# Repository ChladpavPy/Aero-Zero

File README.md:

# Aero-Zero Custom Flight Controller

I started this project, because I wanted to build fully autonomous ai drone. When I looked at the flight controllers available on the market, they were full of hardware that I just do not need or just that I could not add things that I want (for example the Rasberry pi zero 2w) . Most boards also waste a lot of space on powering analog OSD chips, which is completely useless for me because I am flying a purely digital HD system like Walksnail Avatar. Because the technology changed and digital is the standard now, I realized it is just a waste of space to keep the analog stuff and massive connectors.

I am using Raspberry Pi Zero 2W as the computer. Firstly I wanted to use something more powerful to be able to run ai smoother, like allwinner cubie a7z, but it is more expensive and the biggest issue is the firmware and gpio programming on this device. I have no idea, how I would programm this device, when there are basically no manuals or datasheets to this, so I am using the basic raspberry pi zero 2w. So the most interesting thing on this pcb is the pi zero 2w, which is connected to the board by set of pins and screw holes that can be mounted on the pcb by screws.

The drone itself would be able to lift off and fly to a location based on the gps, there is the barometer, from which the drone gets the current altitude and can get to ground. I am using walksnail camera and elrs, plus LIDAR. There is a jst connector for led strip, while at the same time there are built in leds on the drone chassis, esc unit connector and built in electromagnetic buzzer and boot and rst buttons.

The first stage was actually studying the STM32 pinouts and figuring out as much possible of how modern flight controllers handle gyro SPI communication and high speed SDIO routing.

A custom mainboard designed to replace standard generic flight controllers. Built to handle Betaflight high speed kinematics and communicate directly with a Raspberry Pi Zero 2W. Designed entirely from scratch in KiCad 10.

## Project Features

* **Microcontroller:** STM32F405 (100-pin, 32-bit ARM Cortex-M4)
* **Stackup:** 4-Layer PCB (Signal / GND / GND+Power / Signal) for internal routing and better EMI shielding against switching inductors
* **IMU (Gyro):** TDK InvenSense ICM-42688-P connected via dedicated hardware SPI1 bus for high-speed kinematics
* **Barometer:** Goertek SPL06-007 on-board sensor for accurate altitude telemetry
* **Power:** VBAT main input with robust 5V switching regulator (TPS54302) and isolated 3.3V sensor rails
* **Connectivity:** USB-C for main communication with USBLC6 ESD protection, native Raspberry Pi UART interface
* **Digital Video:** Dedicated Walksnail/Caddx VTX JST-SH port (Analog OSD intentionally removed to save space)
* **Storage:** Integrated MicroSD slot (Hirose Push-Pull) routed via high-speed 4-bit SDIO bus for blackbox logging
* **Hardware Protections:** Strict 1:1 hardware pin layout for GPS and LiDAR connectors to prevent accidental voltage shorts during assembly
* **Radio Link:** Dedicated UART port for 2.4GHz ExpressLRS nano receiver.

## Firmware

Since this board is built around a custom STM32F405 microcontroller, it runs on the open-source [Betaflight](https://github.com/betaflight/betaflight) firmware. Instead of writing custom flight control loops from scratch, the firmware setup uses a custom target configuration. You can find the complete pin-mapping and resource file (`AeroZero_BF_Config.txt`) ready in the `Firmware` folder.

## Gallery

### 3D PCB Render

### PCB 

### Schematics

### Mechanical Integration MARK4

### Mechanical Integration CUSTOM AERO-ZERO CAD

---

## Bill of Materials (BOM)

| Component | Qty | Purpose / Description | Price (USD) | Link / Distributor |
| :--- | :---: | :--- | :--- | :--- |
| **Custom PCBA (Aero-Zero)** | 2 | Custom designed 4-layer STM32 flight controller board. Fully assembled via JLCPCB SMT. | $131.50 | JLCPCB |
| **GEPRC GEP-M1025-DQ GPS** | 1 | High-precision positioning data (u-blox M10) with integrated QMC5883L compass and backup DPS310 barometer. | $19.80 | [Banggood](https://www.banggood.com/cs/GEPRC-GEP-M1025-Series-M10-Chip-GPS-Module-for-RC-Drone-FPV-Racing-Helicopter-Quadcopter-RC-Airplane-Car-p-2000868.html?cur_warehouse=CN&ID=6324596&rmmds=search) |
| **SpeedyBee BLS 60A 30x30 4-in-1 ESC** | 1 | Electronic Speed Controller (4-in-1) for driving the primary flight motors | $44.00 | [AliExpress](https://www.aliexpress.com/item/1005010400734832.html) |
| **EMAX ECO II 2207 1700KV Brushless Motor** | 4 | Primary propulsion system providing lift and flight dynamics for the drone chassis | $59.00 | [AliExpress](https://www.aliexpress.com/item/1005001706267138.html) |
| **Raspberry Pi Zero 2 W** | 1 | Secondary AI and computer vision processing unit for autonomous flight capabilities | $20.17 | [RPiShop (Czech Republic)](https://rpishop.cz/raspberry-pi-zero/4311-raspberry-pi-zero-2-w.html) |
| **BETAFPV Nano 2.4GHz ELRS** | 1 | 2.4GHz ExpressLRS receiver with T-Type antenna for reliable, low-latency radio control link. | $9.07 | [Aliexpress](https://a.aliexpress.com/_EHLASWw) |
| **LCSC Discrete Components** | 1 | Bottom-side passive components (SD slot, buzzer, flyback diode, resistors/capacitors) for manual assembly. | $16.21 | lcsc.com |

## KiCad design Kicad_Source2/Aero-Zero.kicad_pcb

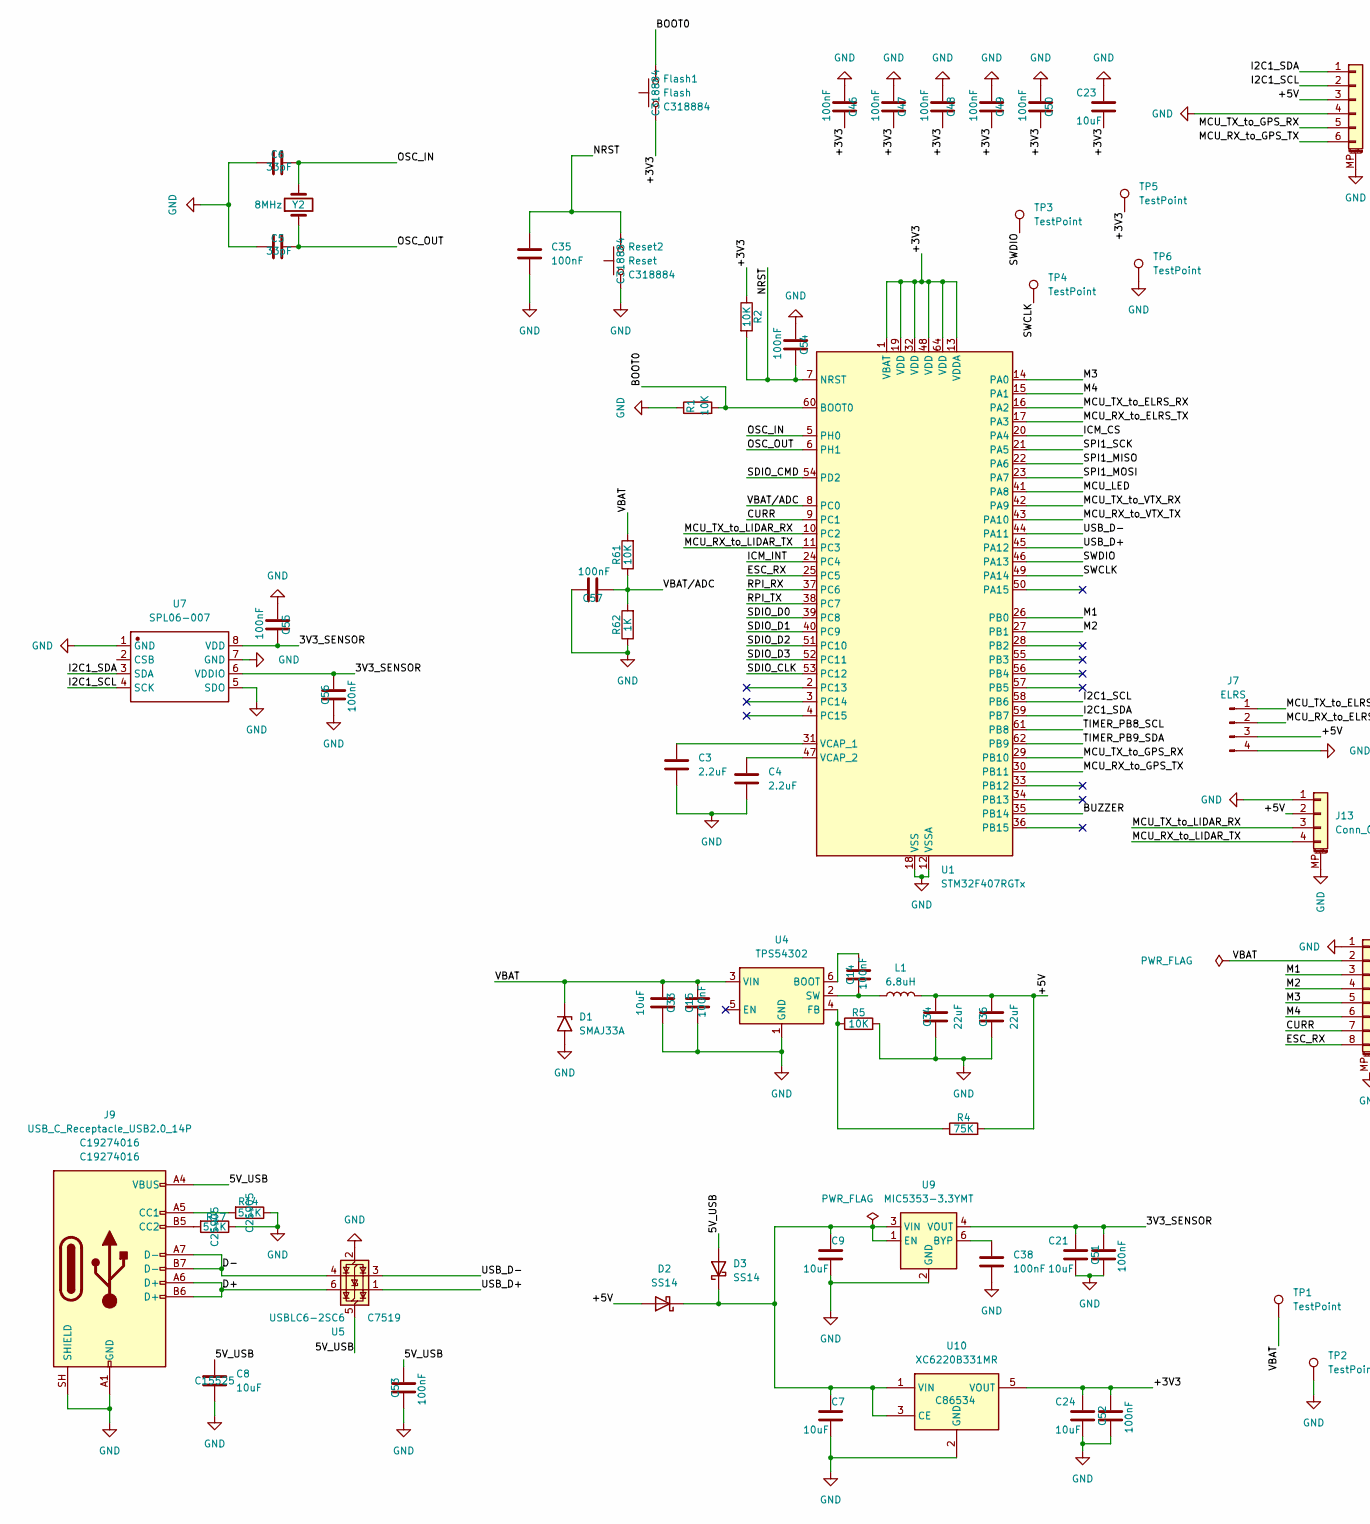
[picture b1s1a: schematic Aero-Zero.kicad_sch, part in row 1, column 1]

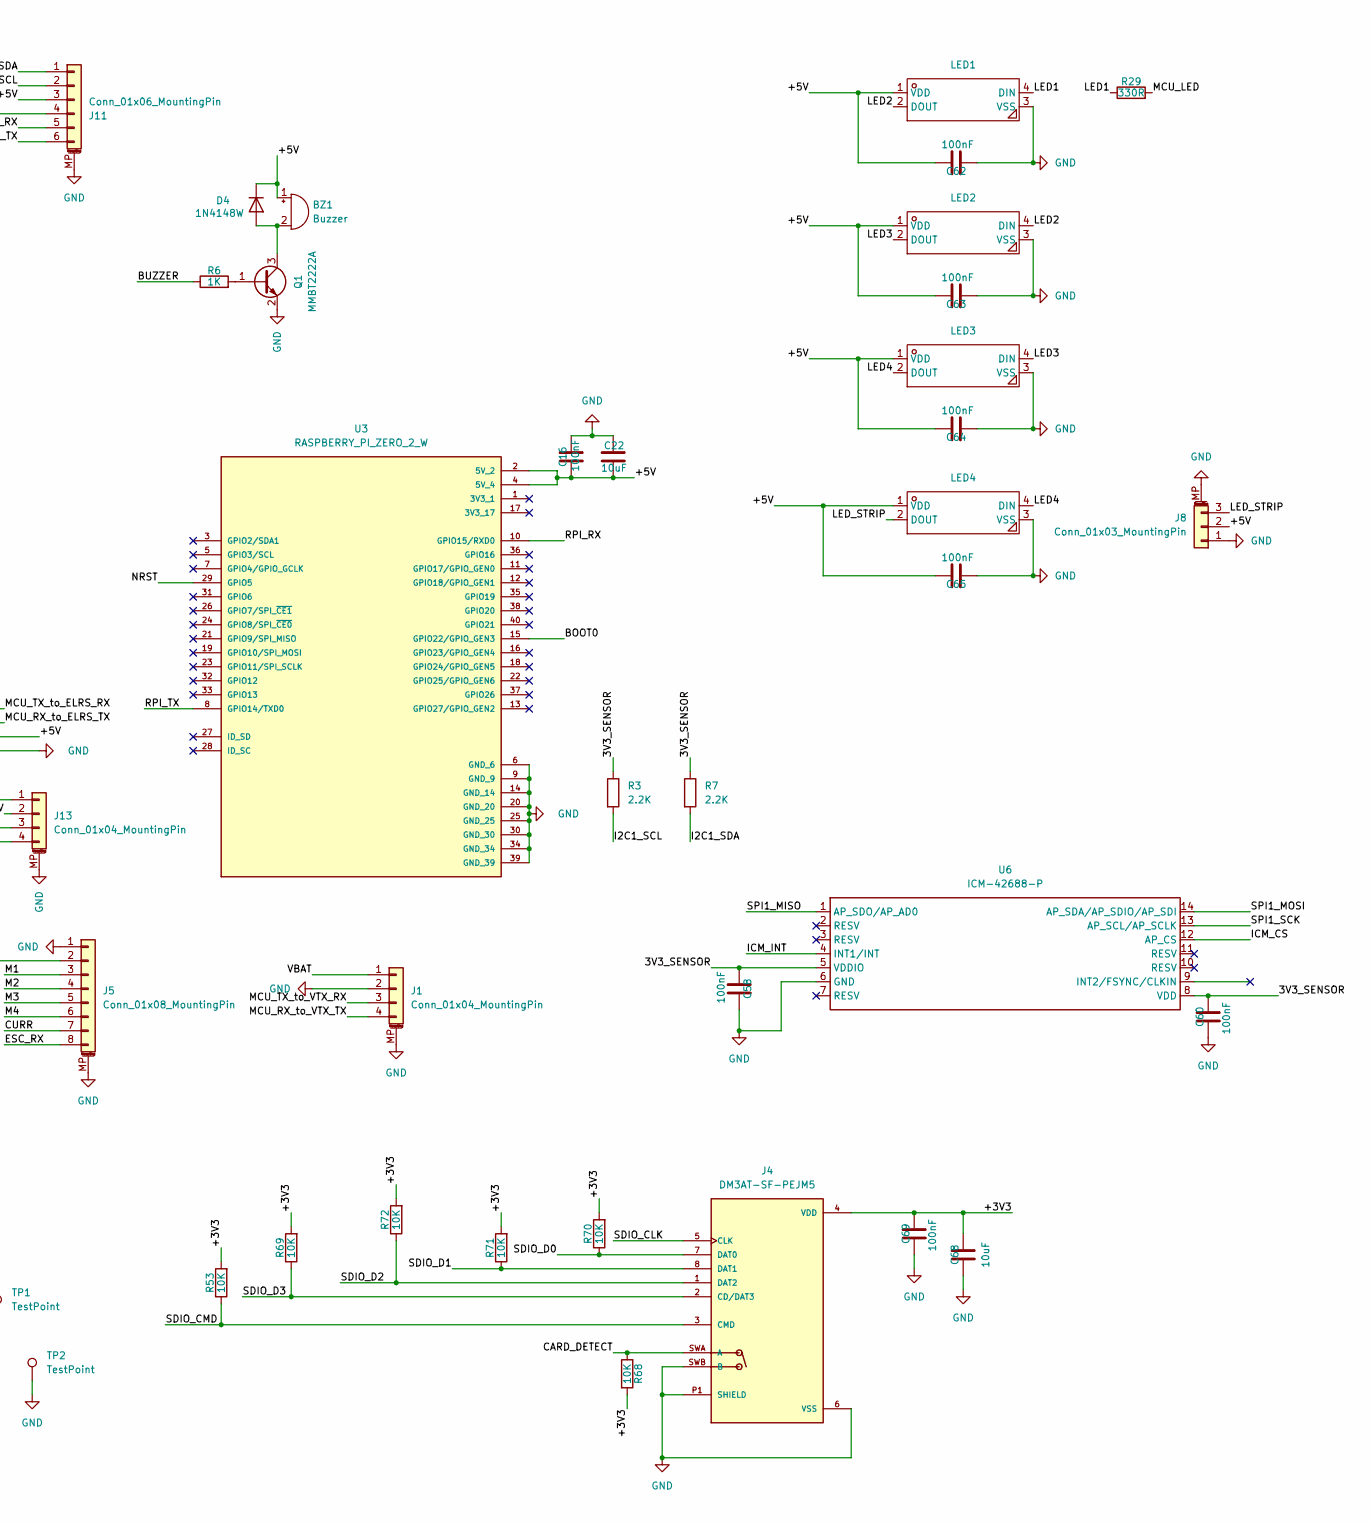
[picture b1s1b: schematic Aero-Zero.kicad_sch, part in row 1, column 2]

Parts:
BZ1: Buzzer; BUZ-SMD_4P-L8.5-W8.5-TL; LCSC C556939
C3, C4: 2.2uF; C_0603_1608Metric; LCSC C23630
C5, C6: 33pF; C_0402_1005Metric; LCSC C1562
C7, C33, C68: 10uF; C_0603_1608Metric; LCSC C19702
C8: 10uF; C_0402_1005Metric; LCSC C15525
C9: 10uF; C_0603_1608Metric; MNF PART NUMBER C15525; LCSC C19702
C14, C15, C16, C46, C47, C48, C49, C50, C51, C52, C53, C54, C55, C56, C57, C58, C60, C62, C63, C64, C65: 100nF; C_0402_1005Metric; LCSC C307331
C21, C24: 10uF; C_0402_1005Metric; MNF PART NUMBER C15525; LCSC C15525
C22, C23: 10uF; C_0805_2012Metric; MNF PART NUMBER C15850; LCSC C15850
C34, C36: 22uF; C_0805_2012Metric; LCSC C45783
C35: 100nF; C_0603_1608Metric; MNF PART NUMBER C14663; LCSC C14663
C38: 100nF; C_0402_1005Metric; MNF PART NUMBER C307331; LCSC C307331
C69: 100nF; C_0603_1608Metric; LCSC C14663
D1: SMAJ33A; D_SMA; LCSC C113966
D2, D3: SS14; D_SMA; LCSC C2480
D4: 1N4148W; D_SOD-123; LCSC C81598
Flash1: Flash; SW_Push_1P1T_XKB_TS-1187A; MNF PART NUMBER C318884; LCSC C318884
J1: Conn_01x04_MountingPin; JST_SH_SM04B-SRSS-TB_1x04-1MP_P1.00mm_Horizontal
J4: DM3AT-SF-PEJM5; HRS_DM3AT-SF-PEJM5_card; PARTREV 20200913; DigiKey_Part_Number HR1964CT-ND
J5: Conn_01x08_MountingPin; JST_SH_SM08B-SRSS-TB_1x08-1MP_P1.00mm_Horizontal
J7: ELRS; PinSocket_1x04_P2.54mm_Vertical
J8: Conn_01x03_MountingPin; JST_SH_SM03B-SRSS-TB_1x03-1MP_P1.00mm_Horizontal
J9: USB_C_Receptacle_USB2.0_14P; USB_C_Receptacle_HCTL_HC-TYPE-C-16P-01A; MNF PART NUMBER C19274016; LCSC C19274016
J11: Conn_01x06_MountingPin; JST_SH_SM06B-SRSS-TB_1x06-1MP_P1.00mm_Horizontal
J13: Conn_01x04_MountingPin; JST_GH_SM04B-GHS-TB_1x04-1MP_P1.25mm_Horizontal
L1: 6.8uH; IND-SMD_L6.0-W6.0_SWPA6045S; LCSC C57254
LED1, LED2, LED3, LED4: LED-SMD_4P-L3.5-W3.5-TL_WS2812B; Manufacturer Part WS2812B-B/T; LCSC Part Name RGB三色
Q1: MMBT2222A; SOT-23; LCSC C8512
R1, R5, R61: 10K; R_0402_1005Metric; LCSC C25804
R2: 10K; C_0603_1608Metric; LCSC C25804
R3, R7: 2.2K; R_0402_1005Metric; LCSC C25879
R4: 75K; R_0603_1608Metric; LCSC C23242
R6: 1K; R_0603_1608Metric; LCSC C21190
R14, R17: 5.1K; R_0402_1005Metric; MNF PART NUMBER C25905; LCSC C25905
R29: 330R; R_0402_1005Metric; LCSC C25104
R53, R68, R69, R70, R71, R72: 10K; R_0603_1608Metric; LCSC C25804
R62: 1K; R_0402_1005Metric; LCSC C11702
Reset2: Reset; SW_Push_1P1T_XKB_TS-1187A; MNF PART NUMBER C318884; LCSC C318884
TP1, TP2: TestPoint; TestPoint_THTPad_D3.0mm_Drill1.5mm
TP3, TP4, TP5, TP6: TestPoint; TestPoint_Pad_1.0x1.0mm
U1: STM32F407RGTx; LQFP-64_10x10mm_P0.5mm; LCSC C15742
U3: RASPBERRY_PI_ZERO_2_W; RpiZero2W_Redukce_Final; PARTREV April 2024
U4: TPS54302; SOT-23-6; LCSC C311983
U5: USBLC6-2SC6; SOT-23-6; MNF PART NUMBER C7519; LCSC C7519
U6: ICM-42688-P; LGA-14_L3.0-W2.5-P0.50-TL; Manufacturer Part ICM-42688-P; LCSC C1850418
U7: SPL06-007; SENSOR-SMD_SPL06-007; Manufacturer Part SPL06-007; LCSC C233787
U9: MIC5353-3.3YMT; MLF-6-1EP_1.6x1.6mm_P0.5mm_EP0.5x1.26mm; LCSC C511311
U10: XC6220B331MR; SOT-23-5; MNF PART NUMBER C86534; LCSC C86534
Y2: 8MHz; Crystal_SMD_5032-2Pin_5.0x3.2mm; LCSC C115962

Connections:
/3V3_SENSOR: C21.1, C51.1, C55.1, C56.1, C58.2, C60.1, R3.1, R7.1, U6.5 (VDDIO), U6.8 (VDD), U7.6 (VDDIO), U7.8 (VDD), U9.4 (VOUT); also elsewhere on the board
/5V_USB: C8.1, C53.1, D3.2 (A), J9.A4 (VBUS), J9.A9 (VBUS), J9.B4 (VBUS), J9.B9 (VBUS), U5.5 (VBUS)
/+3V3: C23.2, C24.1, C46.1, C47.1, C48.1, C49.1, C50.1, C52.1, C68.1, C69.1, Flash1.1, J4.4 (VDD), R2.1, R53.2, R68.2, R69.2, R70.2, R71.2, R72.2, TP5.1 (1_1), U1.1 (VBAT), U1.13 (VDDA), U1.19 (VDD), U1.32 (VDD), U1.48 (VDD), U1.64 (VDD), U10.5 (VOUT); also elsewhere on the board
/+5V: BZ1.1 (+), C16.2, C22.2, C34.1, C36.1, C62.1, C63.1, C64.1, C65.1, D2.2 (A), D4.1 (K), J7.3, J8.2, J11.3, J13.2, L1.2, LED1.1 (VDD), LED2.1 (VDD), LED3.1 (VDD), LED4.1 (VDD), R4.2, U3.2 (5V_2), U3.4 (5V_4)
/BOOT0: Flash1.2, R1.2, U1.60 (BOOT0), U3.15 (GPIO22/GPIO_GEN3)
/BUZZER: R6.1, U1.35 (PB14)
/CARD_DETECT: J4.SWA (A), R68.1
/CURR: J5.7, U1.9 (PC1)
/D+: J9.A6 (D+), J9.B6 (D+), U5.6 (I/O1)
/D-: J9.A7 (D-), J9.B7 (D-), U5.4 (I/O2)
/ESC_RX: J5.8, U1.25 (PC5)
/I2C1_SCL: J11.2, R3.2, U1.58 (PB6), U7.4 (SCK); also elsewhere on the board
/I2C1_SDA: J11.1, R7.2, U1.59 (PB7), U7.3 (SDA); also elsewhere on the board
/ICM_CS: U1.20 (PA4), U6.12 (AP_CS)
/ICM_INT: U1.24 (PC4), U6.4 (INT1/INT)
/LED1: LED1.4 (DIN), R29.1
/LED2: LED1.2 (DOUT), LED2.4 (DIN)
/LED3: LED2.2 (DOUT), LED3.4 (DIN)
/LED4: LED3.2 (DOUT), LED4.4 (DIN)
/LED_STRIP: J8.3, LED4.2 (DOUT)
/M1: J5.3, U1.26 (PB0)
/M2: J5.4, U1.27 (PB1)
/M3: J5.5, U1.14 (PA0)
/M4: J5.6, U1.15 (PA1)
/MCU_LED: R29.2, U1.41 (PA8)
/MCU_RX_to_ELRS_TX: J7.2, U1.17 (PA3)
/MCU_RX_to_GPS_TX: J11.6, U1.30 (PB11)
/MCU_RX_to_LIDAR_TX: J13.4, U1.11 (PC3)
/MCU_RX_to_VTX_TX: J1.4, U1.43 (PA10)
/MCU_TX_to_ELRS_RX: J7.1, U1.16 (PA2)
/MCU_TX_to_GPS_RX: J11.5, U1.29 (PB10)
/MCU_TX_to_LIDAR_RX: J13.3, U1.10 (PC2)
/MCU_TX_to_VTX_RX: J1.3, U1.42 (PA9)
/NRST: C35.1, C54.1, R2.2, Reset2.2, U1.7 (NRST), U3.29 (GPIO5)
/OSC_IN: C6.1, U1.5 (PH0), Y2.2
/OSC_OUT: C5.1, U1.6 (PH1), Y2.1
/RPI_RX: U1.37 (PC6), U3.10 (GPIO15/RXD0)
/RPI_TX: U1.38 (PC7), U3.8 (GPIO14/TXD0)
/SDIO_CLK: J4.5 (CLK), U1.53 (PC12)
/SDIO_CMD: J4.3 (CMD), R53.1, U1.54 (PD2)
/SDIO_D0: J4.7 (DAT0), R70.1, U1.39 (PC8)
/SDIO_D1: J4.8 (DAT1), R71.1, U1.40 (PC9)
/SDIO_D2: J4.1 (DAT2), R72.1, U1.51 (PC10)
/SDIO_D3: J4.2 (CD/DAT3), R69.1, U1.52 (PC11)
/SPI1_MISO: U1.22 (PA6), U6.1 (AP_SDO/AP_AD0)
/SPI1_MOSI: U1.23 (PA7), U6.14 (AP_SDA/AP_SDIO/AP_SDI)
/SPI1_SCK: U1.21 (PA5), U6.13 (AP_SCL/AP_SCLK)
/SWCLK: TP4.1 (1_1), U1.49 (PA14)
/SWDIO: TP3.1 (1_1), U1.46 (PA13)
/TIMER_PB8_SCL: U1.61 (PB8)
/TIMER_PB9_SDA: U1.62 (PB9)
/USB_D+: U1.45 (PA12), U5.1 (I/O1)
/USB_D-: U1.44 (PA11), U5.3 (I/O2)
/VBAT: C15.1, C33.2, D1.1 (A1), J1.1, J5.2, R61.2, TP1.1 (1_1), U4.3 (VIN)
/VBAT/ADC: C57.2, R61.1, R62.2, U1.8 (PC0)
GND: C3.1, C4.2, C5.2, C6.2, C7.2, C8.2, C9.2, C15.2, C16.1, C21.2, C22.1, C23.1, C24.2, C33.1, C34.2, C35.2, C36.2, C38.2, C46.2, C47.2, C48.2, C49.2, C50.2, C51.2, C52.2, C53.2, C54.2, C55.2, C56.2, C57.1, C58.1, C60.2, C62.2, C63.2, C64.2, C65.2, C68.2, C69.2, D1.2 (A2), J1.2, J1.MP (MountPin), J4.6 (VSS), J4.P1 (SHIELD), J4.P2 (SHIELD), J4.P3 (SHIELD), J4.P4 (SHIELD), J4.SWB (B), J5.1, J5.MP (MountPin), J7.4, J8.1, J8.MP (MountPin), J9.A1 (GND), J9.A12 (GND), J9.B1 (GND), J9.B12 (GND), J9.SH (SHIELD), J11.4, J11.MP (MountPin), J13.1, J13.MP (MountPin), LED1.3 (VSS), LED2.3 (VSS), LED3.3 (VSS), LED4.3 (VSS), Q1.2 (E), R1.1, R5.2, R14.1, R17.1, R62.1, Reset2.1, TP2.1 (1_1), TP6.1 (1_1), U1.12 (VSSA), U1.18 (VSS), U1.63 (VSS), U3.6 (GND_6), U3.9 (GND_9), U3.14 (GND_14), U3.20 (GND_20), U3.25 (GND_25), U3.30 (GND_30), U3.34 (GND_34), U3.39 (GND_39), U4.1 (GND), U5.2 (GND), U6.6 (GND), U7.1 (GND), U7.5 (SDO), U7.7 (GND), U9.2 (GND), U9.7 (GND), U10.2 (GND); also elsewhere on the board
unnamed: BZ1.2 (-), D4.2 (A), Q1.3 (C)
unnamed: C7.1, C9.1, D2.1 (K), D3.1 (K), U9.1 (EN), U9.3 (VIN), U10.1 (VIN), U10.3 (CE)
unnamed: J9.A5 (CC1), R14.2
unnamed: J9.B5 (CC2), R17.2
unnamed: Q1.1 (B), R6.2
unnamed: C3.2, U1.31 (VCAP_1)
unnamed: C4.1, U1.47 (VCAP_2)
unnamed: C14.1, U4.6 (BOOT)
unnamed: R4.1, R5.1, U4.4 (FB)
unnamed: C14.2, L1.1, U4.2 (SW)
unnamed: C38.1, U9.6 (BYP)

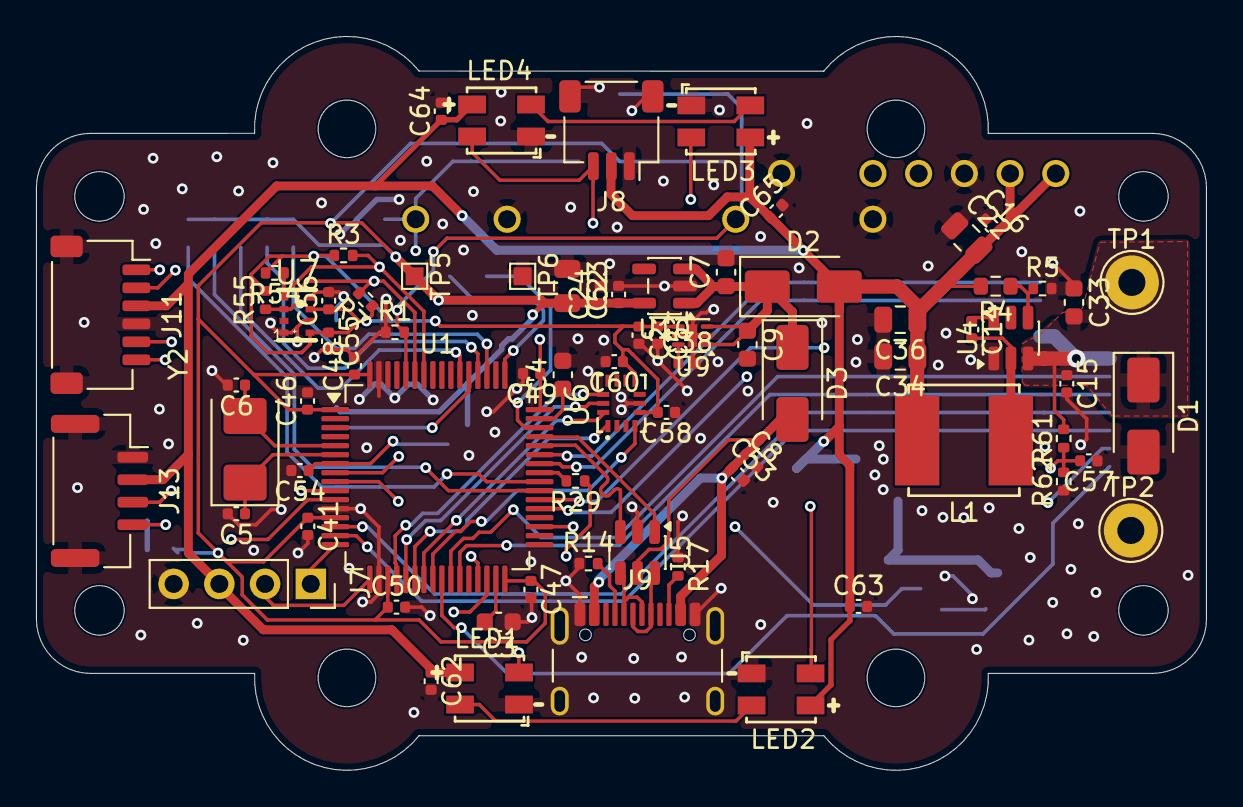
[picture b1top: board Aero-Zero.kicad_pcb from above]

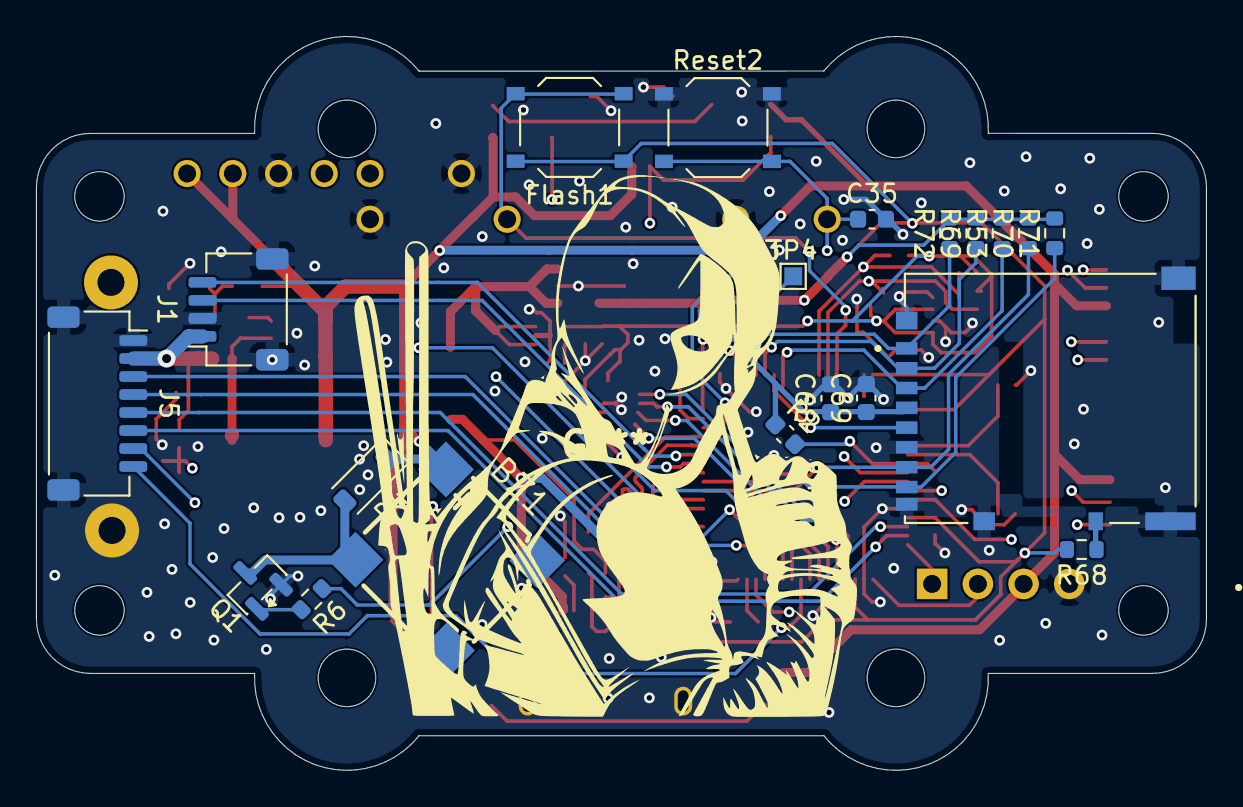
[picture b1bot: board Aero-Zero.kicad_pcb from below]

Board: 4 copper layers, 65.0 x 40.8 mm, 96 parts (21 on the bottom side), 65 nets.

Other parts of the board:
C41: 100nF; C_0402_1005Metric
R54, R55: 2,2K; R_0402_1005Metric

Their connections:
/3V3_SENSOR: R54.2, R55.2; also elsewhere on the board
/+3V3: C41.1; also elsewhere on the board
/I2C1_SCL: R54.1; also elsewhere on the board
/I2C1_SDA: R55.1; also elsewhere on the board
GND: C41.2; also elsewhere on the board

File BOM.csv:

"Reference","Qty","Value","DNP","Exclude from BOM","Exclude from Board","Footprint","Datasheet","LCSC"
"BZ1","1","Buzzer","","","","AeroZero:BUZ-SMD_4P-L8.5-W8.5-P8.50-TL","","C95298"
"C3,C4","2","2.2uF","","","","Capacitor_SMD:C_0603_1608Metric","","C23630"
"C5,C6","2","33pF","","","","Capacitor_SMD:C_0402_1005Metric","","C1562"
"C7,C21,C24","3","10uF","","","","Capacitor_SMD:C_0402_1005Metric","","C15850"
"C8,C9","2","10uF","","","","Capacitor_SMD:C_0402_1005Metric","","C15525"
"C14,C15,C16,C38,C41,C42,C43,C44,C45,C46,C47,C48,C49,C50,C51,C52,C53,C54,C57,C62,C63,C64,C65,C69","24","100nF","","","","Capacitor_SMD:C_0402_1005Metric","","C307331"
"C22,C23","2","10uF","","","","Capacitor_SMD:C_0805_2012Metric","","C15850"
"C33,C68","2","10uF","","","","Capacitor_SMD:C_0603_1608Metric","","C19702"
"C34,C36","2","22uF","","","","Capacitor_SMD:C_0805_2012Metric","","C45783"
"C35","1","100nF","","","","Capacitor_SMD:C_0402_1005Metric","","C1525"
"D1","1","SMAJ33A","","","","Diode_SMD:D_SMA","https://www.littelfuse.com/media?resourcetype=datasheets&ite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","C113966"
"D2,D3","2","SS14","","","","Diode_SMD:D_SMA","https://www.vishay.com/docs/88746/ss12.pdf","C2480"
"D4","1","1N4148W","","","","Diode_SMD:D_SOD-123","https://www.vishay.com/docs/85748/1n4148w.pdf","C81598"
"Flash1","1","Flash","","","","Button_Switch_SMD:SW_Push_1P1T_XKB_TS-1187A","","C318884"
"J1","1","Conn_01x04_MountingPin","","","","Connector_JST:JST_SH_SM04B-SRSS-TB_1x04-1MP_P1.00mm_Horizontal","","C160404"
"J4","1","DM3AT-SF-PEJM5","","","","AeroZero:HRS_DM3AT-SF-PEJM5_card","","C114218"
"J5","1","Conn_01x08_MountingPin","","","","Connector_JST:JST_SH_SM08B-SRSS-TB_1x08-1MP_P1.00mm_Horizontal","","C160408"
"J7","1","ELRS","1","1","","Connector_PinSocket_2.54mm:PinSocket_1x04_P2.54mm_Vertical","",""
"J8","1","Conn_01x03_MountingPin","","","","Connector_JST:JST_SH_SM03B-SRSS-TB_1x03-1MP_P1.00mm_Horizontal","","C160403"
"J9","1","USB_C_Receptacle_USB2.0_14P","","","","Connector_USB:USB_C_Receptacle_HCTL_HC-TYPE-C-16P-01A","https://www.usb.org/sites/default/files/documents/usb_type-c.zip","C19274016"
"J11","1","Conn_01x06_MountingPin","","","","Connector_JST:JST_SH_SM06B-SRSS-TB_1x06-1MP_P1.00mm_Horizontal","","C160406"
"J13","1","Conn_01x04_MountingPin","","","","Connector_JST:JST_GH_SM04B-GHS-TB_1x04-1MP_P1.25mm_Horizontal","","C189785"
"L1","1","6.8uH","","","","AeroZero:IND-SMD_L6.0-W6.0_SWPA6045S","","C57254"
"LED1,LED2,LED3,LED4","4","","","","","AeroZero:LED-SMD_4P-L3.5-W3.5-TL_WS2812B","https://item.szlcsc.com/datasheet/WS2812B-B%252FT/2886707.html","C527089"
"Q1","1","MMBT2222A","","","","Package_TO_SOT_SMD:SOT-23","https://assets.nexperia.com/documents/data-sheet/MMBT2222A.pdf","C8512"
"R1,R2,R5,R53,R61,R68,R69,R70,R71,R72","10","10K","","","","Resistor_SMD:R_0402_1005Metric","","C25804"
"R4","1","75K","","","","Resistor_SMD:R_0603_1608Metric","","C23242"
"R6,R62","2","1K","","","","Resistor_SMD:R_0402_1005Metric","","C11702"
"R14,R17","2","5.1K","","","","Resistor_SMD:R_0402_1005Metric","","C25905"
"R29","1","330R","","","","Resistor_SMD:R_0402_1005Metric","","C25104"
"R54,R55","2","2,2K","","","","Resistor_SMD:R_0402_1005Metric","","C25879"
"Reset2","1","Reset","","","","Button_Switch_SMD:SW_Push_1P1T_XKB_TS-1187A","","C318884"
"TP1,TP2","2","TestPoint","1","1","","TestPoint_THTPad_D3.0mm_Drill1.5mm","",""
"TP3,TP4,TP5,TP6","4","TestPoint","1","1","","TestPoint:TestPoint_Pad_1.0x1.0mm","",""
"U1","1","STM32F407RGTx","","","","Package_QFP:LQFP-64_10x10mm_P0.5mm","https://www.st.com/resource/en/datasheet/stm32f405rg.pdf","C15742"
"U2","1","DPS310XTSA1","","","","AeroZero:XDCR_DPS310XTSA1","","C130156"
"U3","1","RASPBERRY_PI_ZERO_2_W","1","1","","AeroZero:RpiZero2W_Redukce_Final","",""
"U4","1","TPS54302","","","","Package_TO_SOT_SMD:SOT-23-6","http://www.ti.com/lit/ds/symlink/tps54302.pdf","C311983"
"U5","1","USBLC6-2SC6","","","","Package_TO_SOT_SMD:SOT-23-6","https://www.st.com/resource/en/datasheet/usblc6-2.pdf","C7519"
"U8","1","BMI270","","","","AeroZero:XDCR_BMI270","","C2836813"
"U9","1","MIC5353-3.3YMT","","","","Package_DFN_QFN:MLF-6-1EP_1.6x1.6mm_P0.5mm_EP0.5x1.26mm","http://ww1.microchip.com/downloads/en/DeviceDoc/mic5353.pdf","C511311"
"U10","1","XC6220B331MR","","","","Package_TO_SOT_SMD:SOT-23-5","https://www.torexsemi.com/file/xc6220/XC6220.pdf","C86534"
"Y2","1","8MHz","","","","Crystal:Crystal_SMD_5032-2Pin_5.0x3.2mm","","C115962"

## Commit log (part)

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2026-05-21 Expand README with project details and BOM
    Added detailed project description, features, gallery, and bill of materials for the Aero-Zero Custom Flight Controller.
2026-05-21 Change PCB render images from JPG to PNG
    Updated image file extensions from .jpg to .png for 3D PCB renders.
2026-05-21 Rename Snímek obrazovky 2026-05-21 143457.png to schematics.png
2026-05-21 Rename Snímek obrazovky 2026-05-21 143509.png to pcb_b.png
2026-05-21 Rename Snímek obrazovky 2026-05-21 143522.png to pcb_in1.png
2026-05-21 Rename Snímek obrazovky 2026-05-21 143519.png to pcb_f.png
2026-05-21 Rename Snímek obrazovky 2026-05-21 143514.png to pcb_in2.png
2026-05-21 Add PCB and Schematics sections with images
2026-05-21 Rename Snímek obrazovky 2026-05-21 143424.png to schematics2.png
2026-05-21 Replace Fusion 360 Assembly images in README
    Updated images in the Mechanical Integration section.
2026-05-21 Update Fusion 360 assembly image in README
2026-05-21 Remove PCB images placeholder text
    Removed placeholder text for PCB images.
2026-05-21 Modify GPS Module pricing and distributor link
    Updated the price and link for the GPS Module FLYWOO GOKU GM10 Mini V3.
2026-05-21 Add price for Custom PCBA in Bill of Materials
    Added price for Custom PCBA (Aero-Zero) in the BOM.
2026-06-14 Fix image filename case for schematics
    Updated image filename for schematics to match case sensitivity.
2026-06-14 Revise microcontroller and BOM details in README
    Updated microcontroller and IMU details in the project features section. Adjusted prices and added new components in the Bill of Materials.
2026-06-14 Add radio link information to README
2026-06-14 Update price for LCSC Discrete Components
    Updated the price for LCSC Discrete Components in the README.
